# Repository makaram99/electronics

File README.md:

<h1 align="center">Electronics Projects</h1>

---

## 🔑 Introduction

This repository contains some of the electronics projects I have done during my time at the University.

The projects are **open source** and you can use it for your own projects.

## Table of Contents

- [🔑 Introduction](#-introduction)
- [Table of Contents](#table-of-contents)
- [Repo Hierarchy](#repo-hierarchy)
- [🎯 Samples](#-samples)
- [💁‍♂️ Contribute](#️-contribute)
- [📞 Contact me](#-contact-me)
- [🔓 Licenses](#-licenses)
- [🔏 Credits](#-credits)

---

## Repo Hierarchy

**The Repo contains:**

* **[assets](assets/)**: Contains some helper files used in documentation of this repo.
* **[circuits](circuits/)**: Contains electronic circuits to be used in larger projects.
* **[simulation](simulation/)**: Contains electronics projects.

**Projects & Circuits consists of:**

* Simulation files using either Proteus or Multisim
* PCB files using either Eagle or Altium
* Electrical Analysis of the circuit
* Resources for the circuit or project

---

## 🎯 Samples

The following are some of the projects and circuits.

**NOTE**: Click on the proteus images below to start the animation.

1. **PIC16F877A Microcontroller Kit:**

2. **Power Circruit:**

3. **Arrows Keypad:**

4. **IR Array:**

---

## 💁‍♂️ Contribute

If you want to contribute to the project, you can:

1. Fork the project on your GitHub account.
2. Develop the project on your own.
3. Send a pull request to the project on GitHub.
4. I will review your pull request and add it to the project.

---

## 📞 Contact me

<p>  </p>

## 🔓 Licenses

<br />All DOCUMENTS inside this work is licensed under a <a rel="license" href="http://creativecommons.org/licenses/by-sa/4.0/">Creative Commons Attribution-ShareAlike 4.0 International License</a>.

All SOURCE codes & BINARIES are licensed under Mit License.

---

## 🔏 Credits

All credits and external sources are listed inside the page and inside this repo, references themselves.

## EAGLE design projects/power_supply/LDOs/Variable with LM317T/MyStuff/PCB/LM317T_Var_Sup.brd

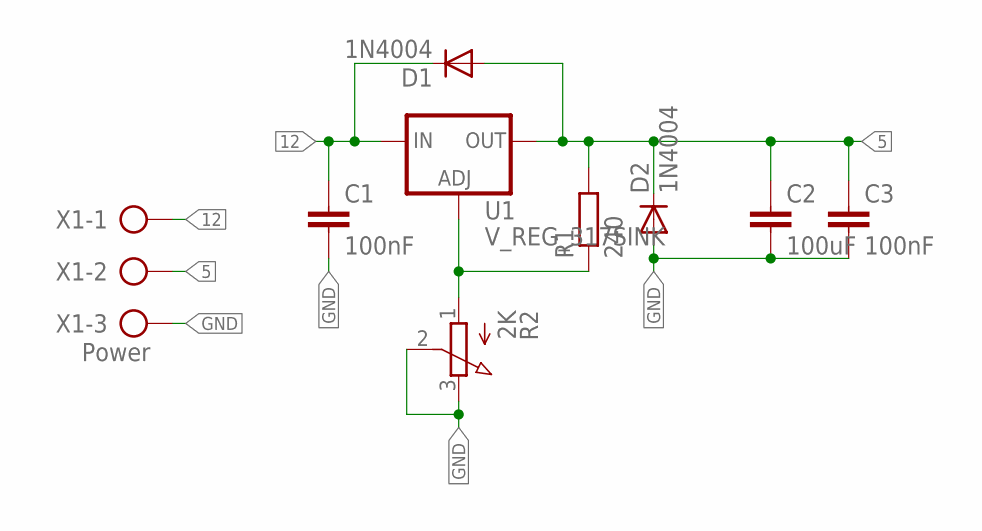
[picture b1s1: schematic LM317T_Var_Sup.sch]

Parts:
C1, C3: 100nF; C2.5-2
C2: 100uF; C5B5
D1, D2: 1N4004; DO41-10
R1: 240; 0207/7
R2: 2K; 3RP/1610N
U1: V_REG_317SINK; TO220-ADJ
X1: Power; AK500/3-H

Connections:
5: C2.1, C3.1, D1.A, D2.C, R1.2, U1.OUT, X1.2
12: C1.1, D1.C, U1.IN, X1.1
GND: C1.2, C2.2, C3.2, D2.A, R2.2 (S), R2.3 (E), X1.3
unnamed: R1.1, R2.1 (A), U1.ADJ

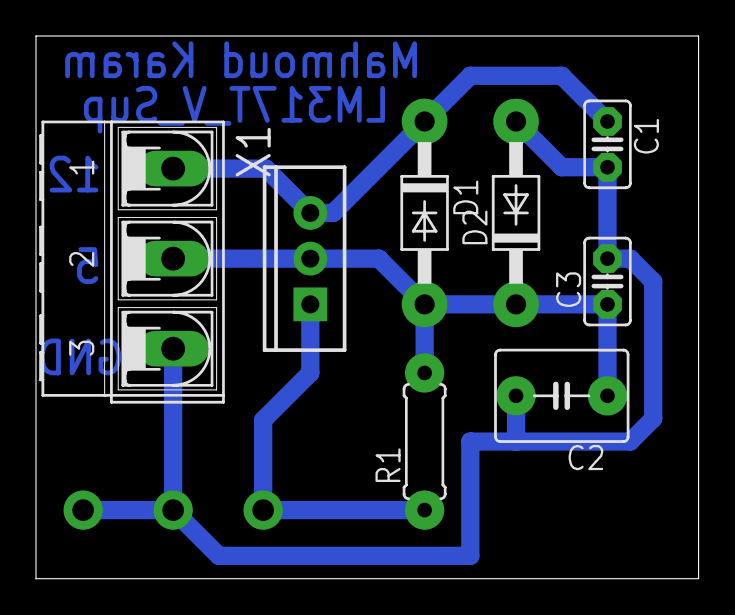
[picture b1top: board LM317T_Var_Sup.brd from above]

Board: 2 copper layers, 36.8 x 30.1 mm, 9 parts (1 on the bottom side), 4 nets.

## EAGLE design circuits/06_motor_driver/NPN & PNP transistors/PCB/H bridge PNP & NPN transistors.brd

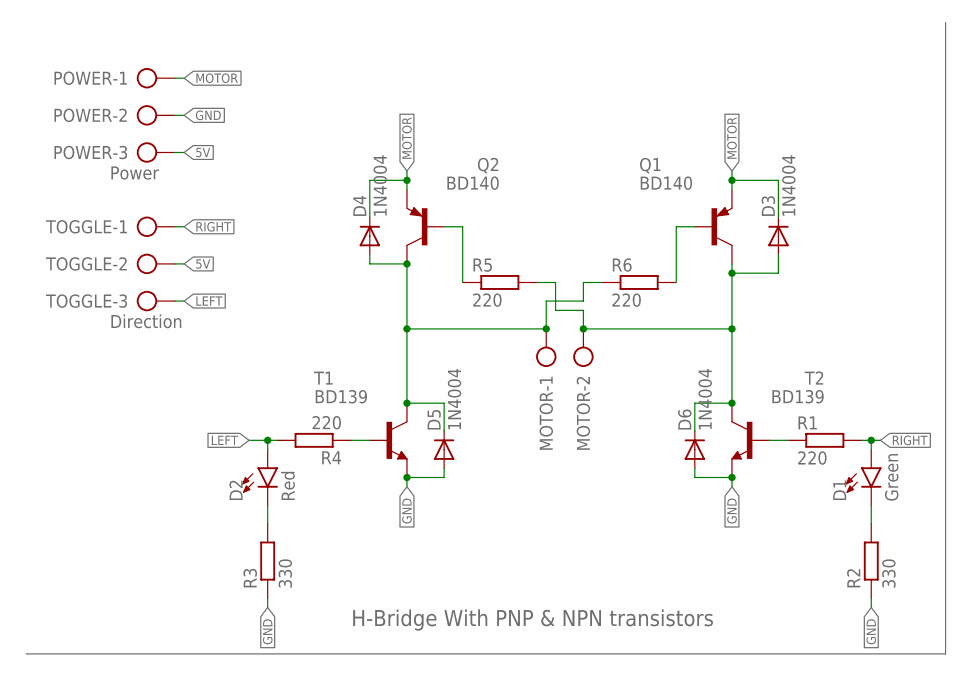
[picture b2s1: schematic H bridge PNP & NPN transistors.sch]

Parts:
D1: Green; LED_5MM
D2: Red; LED_5MM
D3, D4, D5, D6: 1N4004; DO41-10
MOTOR: AK500/2-H
POWER: Power; AK500/3-H
Q1, Q2: BD140; TO126
R1, R4, R5, R6: 220; 0207/7
R2, R3: 330; 0207/7
T1, T2: BD139; TO126
TOGGLE: Direction; AK500/3-H

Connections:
5V: POWER.3, TOGGLE.2
GND: D5.A, D6.A, POWER.2, R2.1, R3.1, T1.1 (E), T2.1 (E)
LEFT: D2.A, R4.2, TOGGLE.3
MOTOR: D3.C, D4.C, POWER.1, Q1.1 (E), Q2.1 (E)
unnamed: D4.A, D5.C, MOTOR.1, Q2.2 (C), R6.1, T1.2 (C)
unnamed: Q2.3 (B), R5.1
unnamed: D3.A, D6.C, MOTOR.2, Q1.2 (C), R5.2, T2.2 (C)
unnamed: Q1.3 (B), R6.2
unnamed: D2.K (C), R3.2
unnamed: R4.1, T1.3 (B)
unnamed: D1.K (C), R2.2
unnamed: R1.1, T2.3 (B)
RIGHT: D1.A, R1.2, TOGGLE.1

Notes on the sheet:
H-Bridge With PNP & NPN transistors

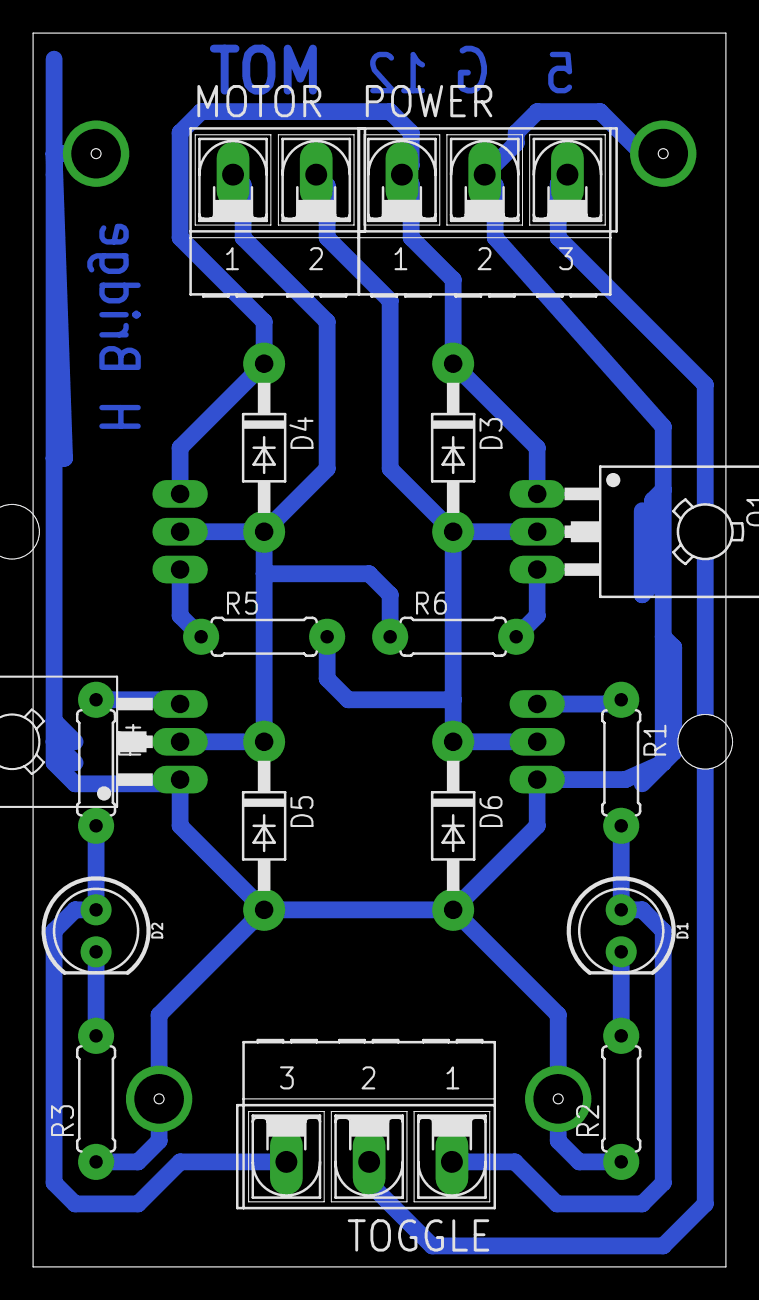
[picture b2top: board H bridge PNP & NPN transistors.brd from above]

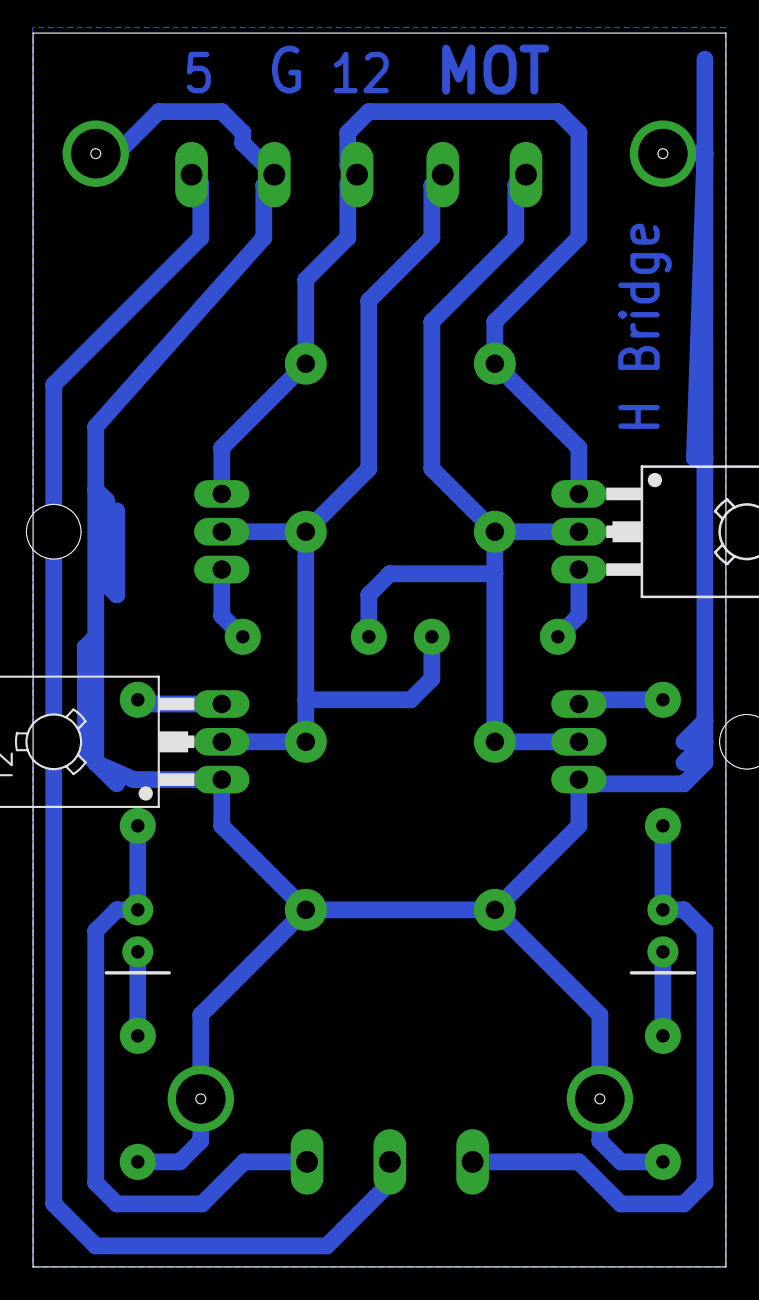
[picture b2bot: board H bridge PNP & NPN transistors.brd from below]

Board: 2 copper layers, 41.9 x 74.6 mm, 19 parts (2 on the bottom side), 13 nets.

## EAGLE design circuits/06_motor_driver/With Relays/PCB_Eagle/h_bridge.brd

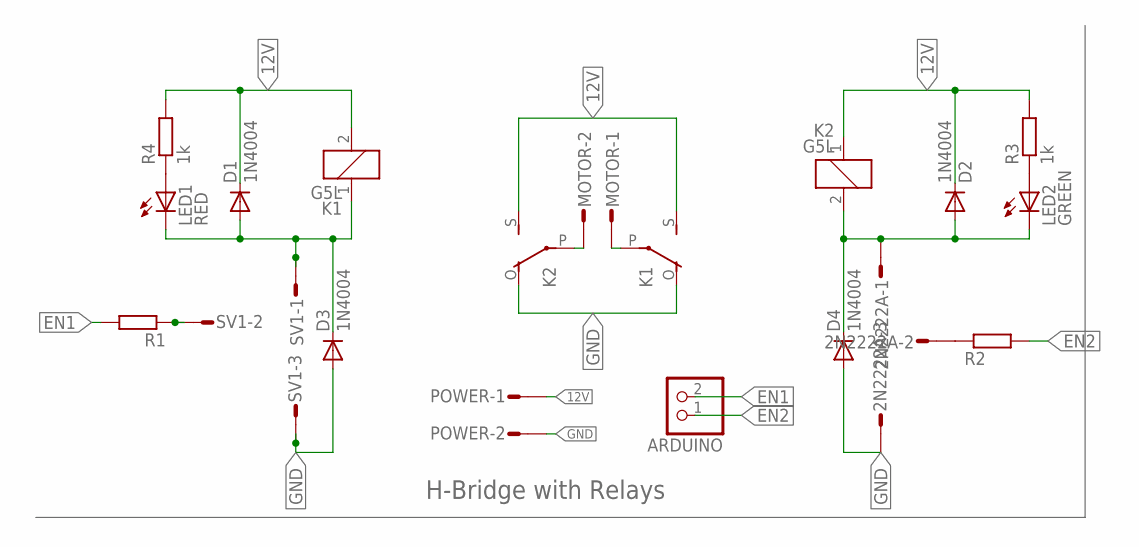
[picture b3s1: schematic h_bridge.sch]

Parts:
2N2222A: MT6-3
ARDUINO: PINHD-1X2; 1X02
D1, D2, D3, D4: 1N4004; DO41-10
K1, K2: G5L; G5LE
LED1: RED; LED3MM
LED2: GREEN; LED3MM
MOTOR: L02P
POWER: L02P
R1, R2: R-EU_0207/7; 0207/7
R3, R4: 1k; 0207/7
SV1: MT6-3

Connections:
12V: D1.C, D2.C, K1.2, K1.S, K2.1, K2.S, POWER.1, R3.2, R4.2
EN1: ARDUINO.2, R1.2
EN2: ARDUINO.1, R2.2
GND: 2N2222A.3, D3.A, D4.A, K1.O, K2.O, POWER.2, SV1.3
unnamed: R1.1, SV1.2
unnamed: D1.A, D3.C, K1.1, LED1.K (C), SV1.1
unnamed: 2N2222A.2, R2.1
unnamed: LED2.A, R3.1
unnamed: 2N2222A.1, D2.A, D4.C, K2.2, LED2.K (C)
unnamed: LED1.A, R4.1
unnamed: K2.P, MOTOR.2
unnamed: K1.P, MOTOR.1

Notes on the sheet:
H-Bridge with Relays

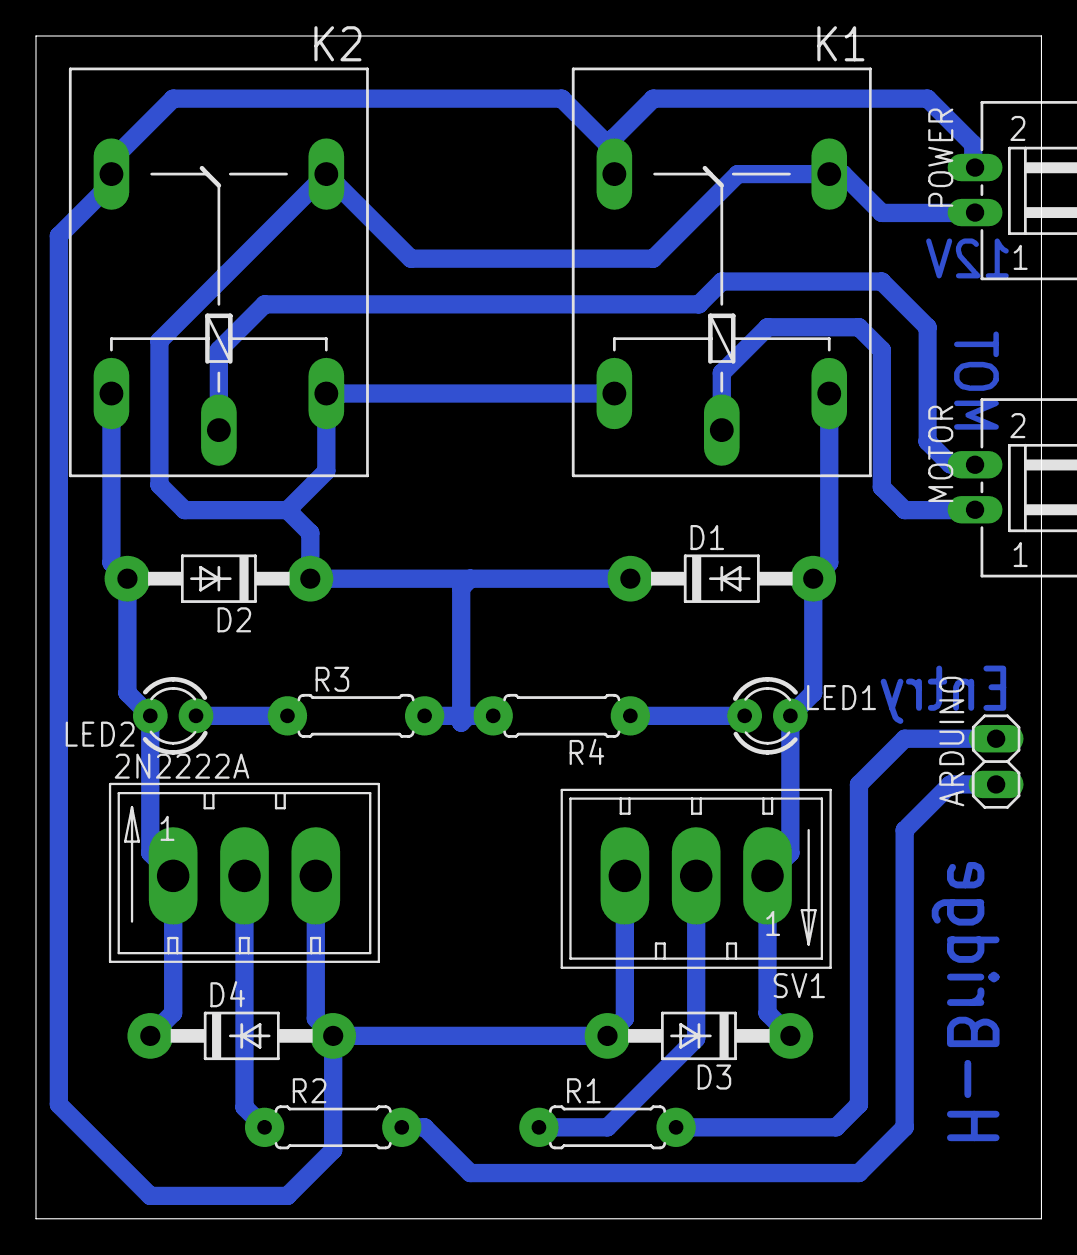
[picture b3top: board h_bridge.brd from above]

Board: 2 copper layers, 55.9 x 65.7 mm, 17 parts (0 on the bottom side), 12 nets.

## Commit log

2022-06-29 Circuits, Projects, and README file added

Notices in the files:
README.md:
License: Mit
parts and their libraries:
SparkFun-LED: Licensing: Creative Commons ShareAlike 4.0 International - https://creativecommons.org/licenses/by-sa/4.0
